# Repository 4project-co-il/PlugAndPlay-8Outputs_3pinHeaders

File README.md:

# PlugAndPlay: Output module with 8 channels, 3pin male headers
This is the repository with the files for PlugAndPlay output module with 8 channels, based on PCA9685 chip.

That module has 8 sets of 3pin male headers, arranged for servo motors connection.
The module also have 1 power port connectors.

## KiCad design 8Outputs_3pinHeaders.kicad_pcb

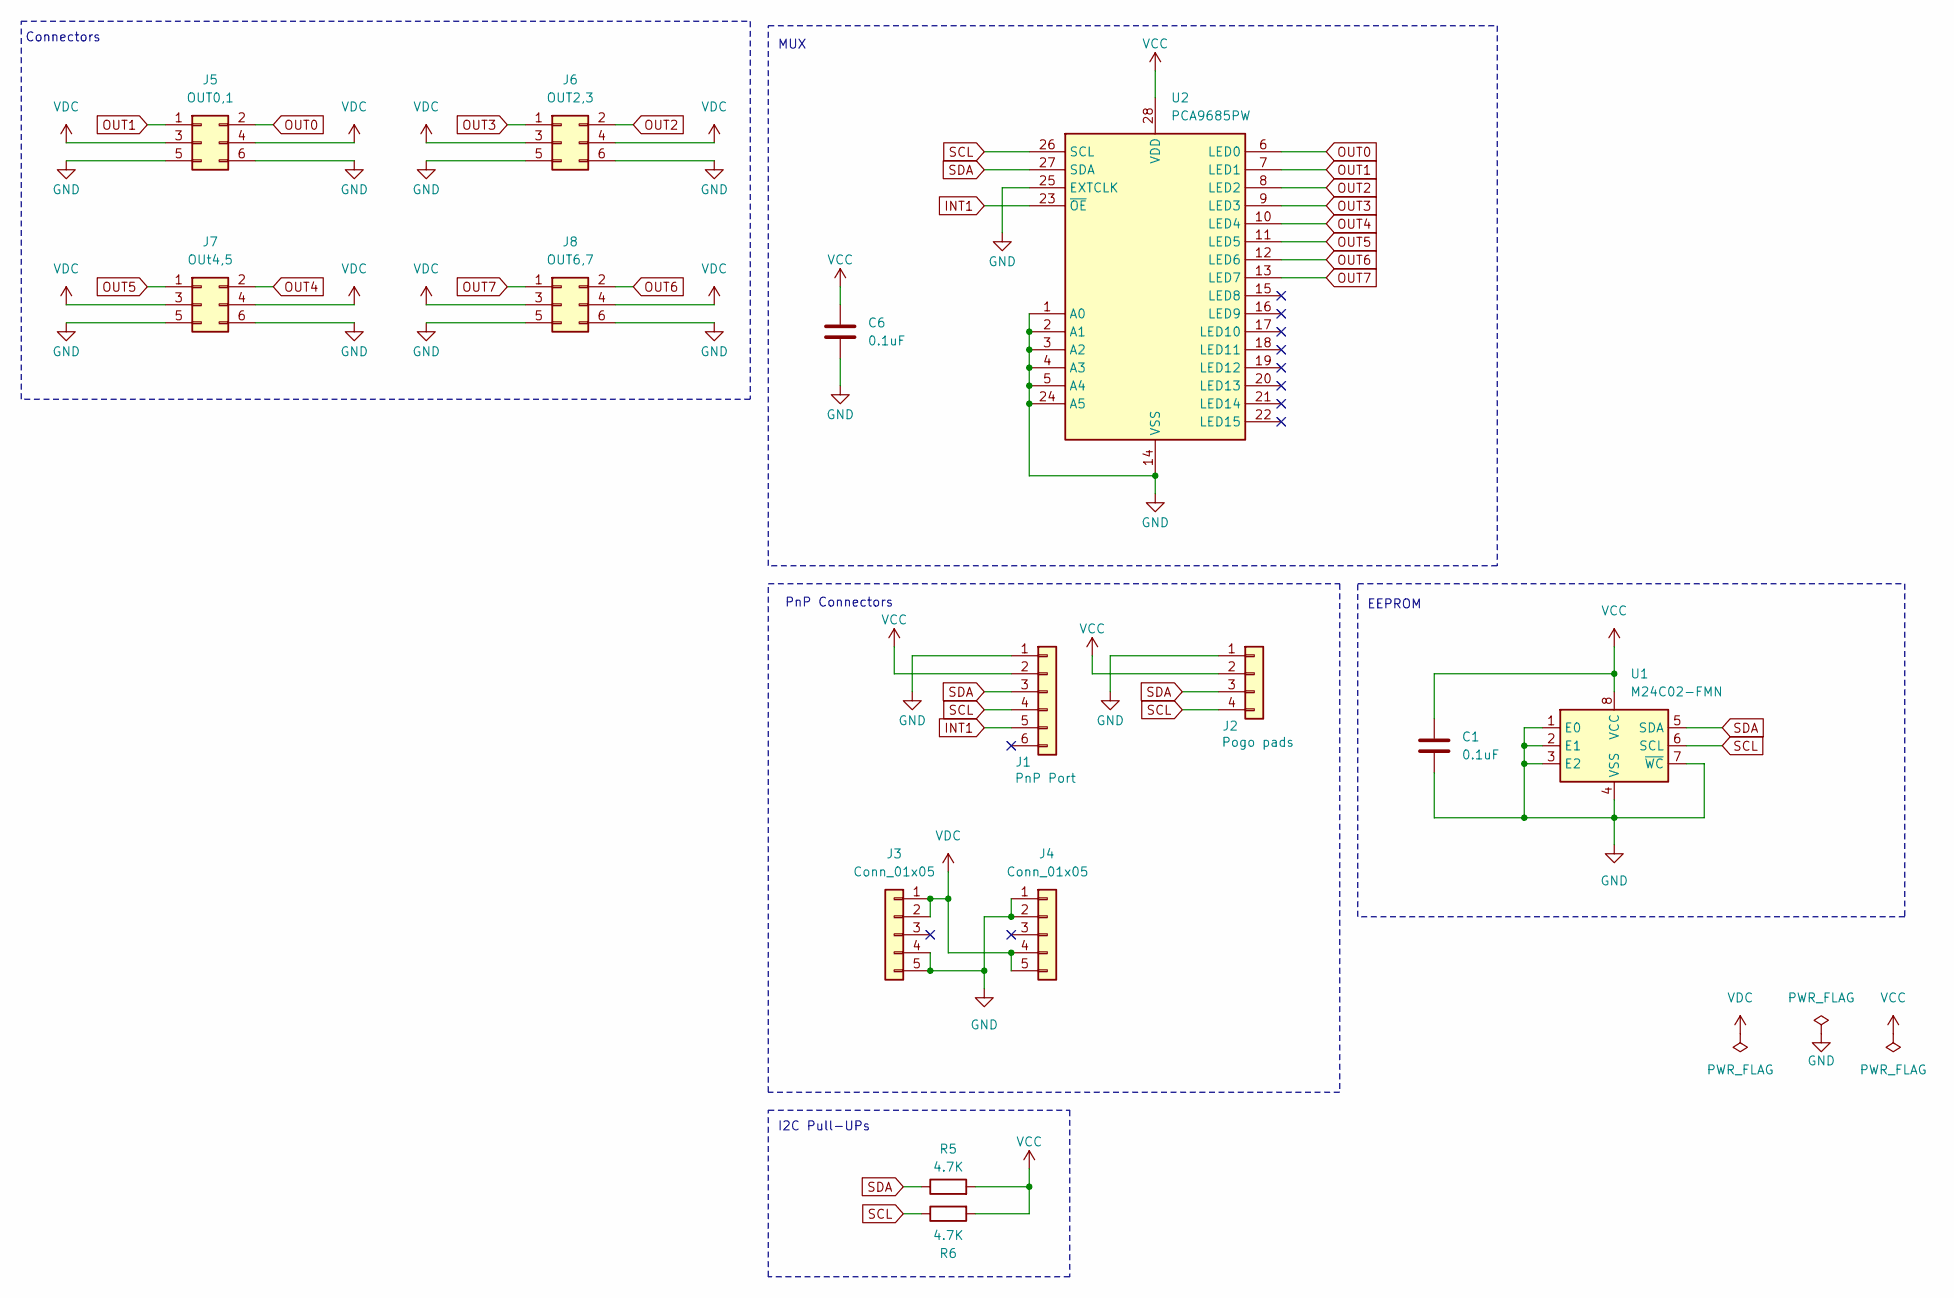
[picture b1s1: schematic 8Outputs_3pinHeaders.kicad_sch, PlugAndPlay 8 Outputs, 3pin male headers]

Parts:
C1, C6: 0.1uF; C_0603_1608Metric; MPN C14663
J1: JST_SH_SM06B-SRSS-TB_1x06-1MP_P1.00mm_Horizontal; MPN C7430448
J2: Conn_01x04; PogoPinsPads_1x04_P2.5mm
J3: Conn_01x05; PinSocket_1x05_P2.54mm_Vertical_SMD_Pin1Right; MPN RealRun
J4: Conn_01x05; PinSocket_1x05_P2.54mm_Vertical_SMD_Pin1Left; MPN RealRun
J5: OUT0,1; PinHeader_2x03_P2.54mm_Vertical_SMD; MPN C53244533
J6: OUT2,3; PinHeader_2x03_P2.54mm_Vertical_SMD; MPN C53244533
J7: OUt4,5; PinHeader_2x03_P2.54mm_Vertical_SMD; MPN C53244533
J8: OUT6,7; PinHeader_2x03_P2.54mm_Vertical_SMD; MPN C53244533
R5, R6: 4.7K; R_0603_1608Metric; MPN C4190
U1: M24C02-FMN; SOIC-8_3.9x4.9mm_P1.27mm; MPN C114502
U2: PCA9685PW; TSSOP-28_4.4x9.7mm_P0.65mm

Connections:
GND: C1.2, C6.2, J1.1, J2.1, J3.4, J3.5, J4.1, J4.2, J5.5, J5.6, J6.5, J6.6, J7.5, J7.6, J8.5, J8.6, U1.1 (E0), U1.2 (E1), U1.3 (E2), U1.4 (VSS), U1.7 (~WC), U2.1 (A0), U2.2 (A1), U2.3 (A2), U2.4 (A3), U2.5 (A4), U2.14 (VSS), U2.24 (A5), U2.25 (EXTCLK)
INT1: J1.5, U2.23 (~OE)
OUT0: J5.2, U2.6 (LED0)
OUT1: J5.1, U2.7 (LED1)
OUT2: J6.2, U2.8 (LED2)
OUT3: J6.1, U2.9 (LED3)
OUT4: J7.2, U2.10 (LED4)
OUT5: J7.1, U2.11 (LED5)
OUT6: J8.2, U2.12 (LED6)
OUT7: J8.1, U2.13 (LED7)
SCL: J1.4, J2.4, R6.1, U1.6 (SCL), U2.26 (SCL)
SDA: J1.3, J2.3, R5.1, U1.5 (SDA), U2.27 (SDA)
VCC: C1.1, C6.1, J1.2, J2.2, R5.2, R6.2, U1.8 (VCC), U2.28 (VDD)
VDC: J3.1, J3.2, J4.4, J4.5, J5.3, J5.4, J6.3, J6.4, J7.3, J7.4, J8.3, J8.4

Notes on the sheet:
EEPROM
MUX
PnP Connectors
I2C Pull-UPs
Connectors

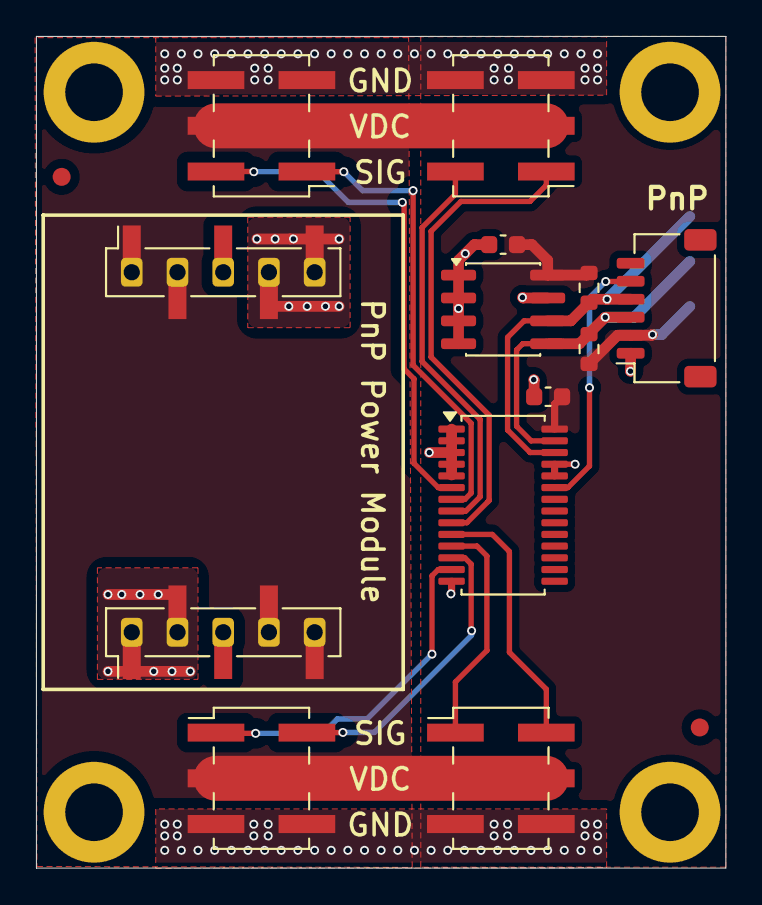
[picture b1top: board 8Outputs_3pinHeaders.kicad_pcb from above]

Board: 2 copper layers, 38.3 x 46.2 mm, 14 parts (1 on the bottom side), 14 nets.
